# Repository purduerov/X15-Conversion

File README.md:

# Readme for X15-Conversion

Whenever you make a new part, download the datasheet and save it here _**and**_ with the part in the parts library

Always pull other people's changes before beginning to work
`git pull`

Be sure to push your changes after  working on them. Run:
1. `git add .` to add any files in this directory or a subdirectory
or `git add -u` to add any modified files
2. (Optional) `git clean -nX` to see what ignored files can be removed
	`git clean -fX` removes ignored files (Eagle backups)
3. `git commit -m "helpful commit message"` with a description of the work that you did
4. `git push` to push your work to github

Other helpful commands
* `git status` says information about modified and staged files
* `git log` shows the recent commits of the repository
* `git log filename.extension` show the recent commits for just that file
* `git checkout first-couple-letter-of-commit-id` lets you go back to a previous version
* `git checkout master` brings you back to the latest commit
* `git tag` lists the tags
* `git tag -a orderX -m "the version of the board placed for the X'th order"` tag a specific commit
* `git push --tags` needed to push tags to remote
* `git show orderX` show the commit log for the given tag
* `git checkout orderX` go back and interact with the files at the tagged commit

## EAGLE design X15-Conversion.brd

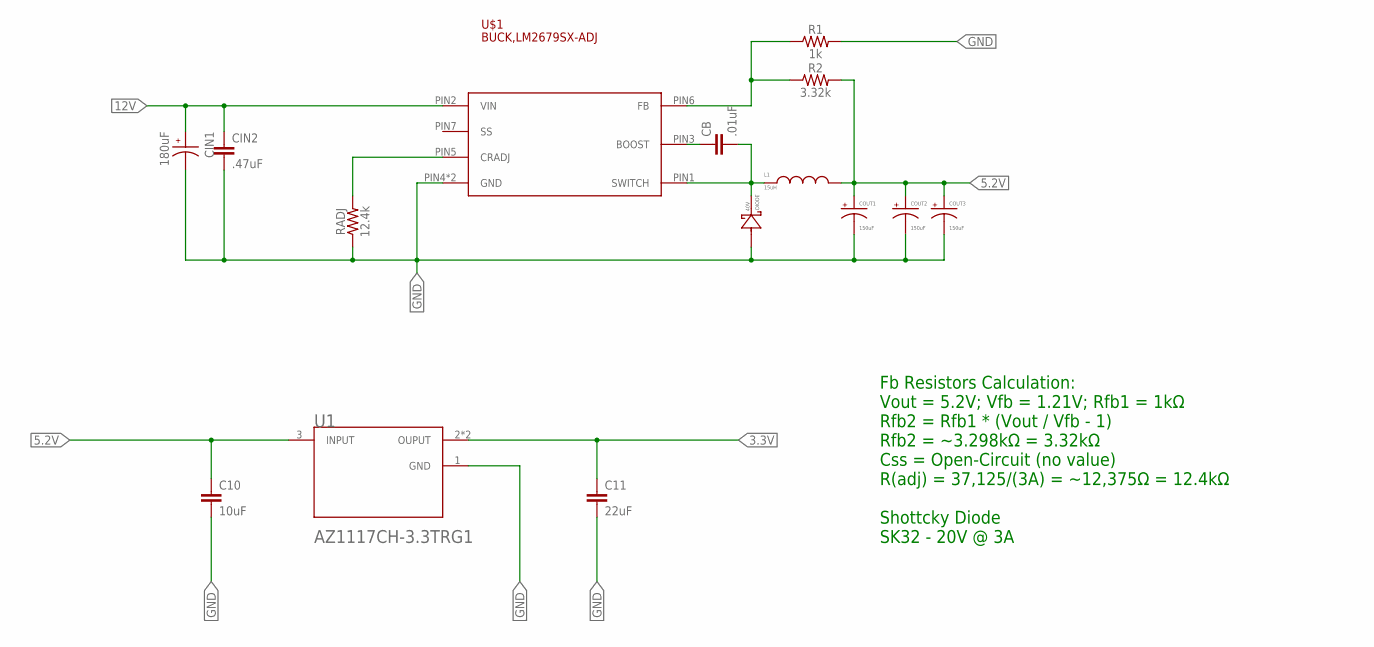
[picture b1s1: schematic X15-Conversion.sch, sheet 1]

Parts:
C10: 10uF; 0603
C11: 22uF; 0603
CB: .01uF; 0603
CIN1: 180uF; CAP_EEEFKE181XSP
CIN2: .47uF; 0603
COUT1, COUT2, COUT3: 150uF; 2917(7343-31-METRIC)
DIODE: 40V; DO214AC
L1: 15uH; HCMA1305
R1: 1k; 0603
R2: 3.32k; 0603
RADJ: 12.4k; 0603
U1: LINEAR,AZ1117CR-3.3TRG1DIODES_AZ1117CH-3.3TRG1_0_0; LINEAR,AZ1117CR-3.3TRG1
U$1: BUCK,LM2679SX-ADJ

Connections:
3.3V: C11.1, U1.2 (OUPUT), U1.4 (OUPUT); also elsewhere on the board
5.2V: C10.1, COUT1.+, COUT2.+, COUT3.+, L1.2, R2.2, U1.3 (INPUT); also elsewhere on the board
12V: CIN1.1, CIN2.1, U$1.PIN2 (VIN); also elsewhere on the board
BOOST: CB.1, U$1.PIN3 (BOOST)
CRADJ: RADJ.2, U$1.PIN5 (CRADJ)
FB: R1.1, R2.1, U$1.PIN6 (FB)
GND: C10.2, C11.2, CIN1.2, CIN2.2, COUT1.-, COUT2.-, COUT3.-, DIODE.A (2), R1.2, RADJ.1, U1.1 (GND), U$1.PIN4 (GND), U$1.PIN8 (GND); also elsewhere on the board
SWITCH: CB.2, DIODE.C (1), L1.1, U$1.PIN1 (SWITCH)

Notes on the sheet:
Fb Resistors Calculation: Vout = 5.2V; Vfb = 1.21V; Rfb1 = 1kΩ Rfb2 = Rfb1 * (Vout / Vfb - 1) Rfb2 = ~3.298kΩ = 3.32kΩ Css = Open-Circuit (no value) R(adj) = 37,125/(3A) = ~12,375Ω = 12.4kΩ Shottcky Diode SK32 - 20V @ 3A

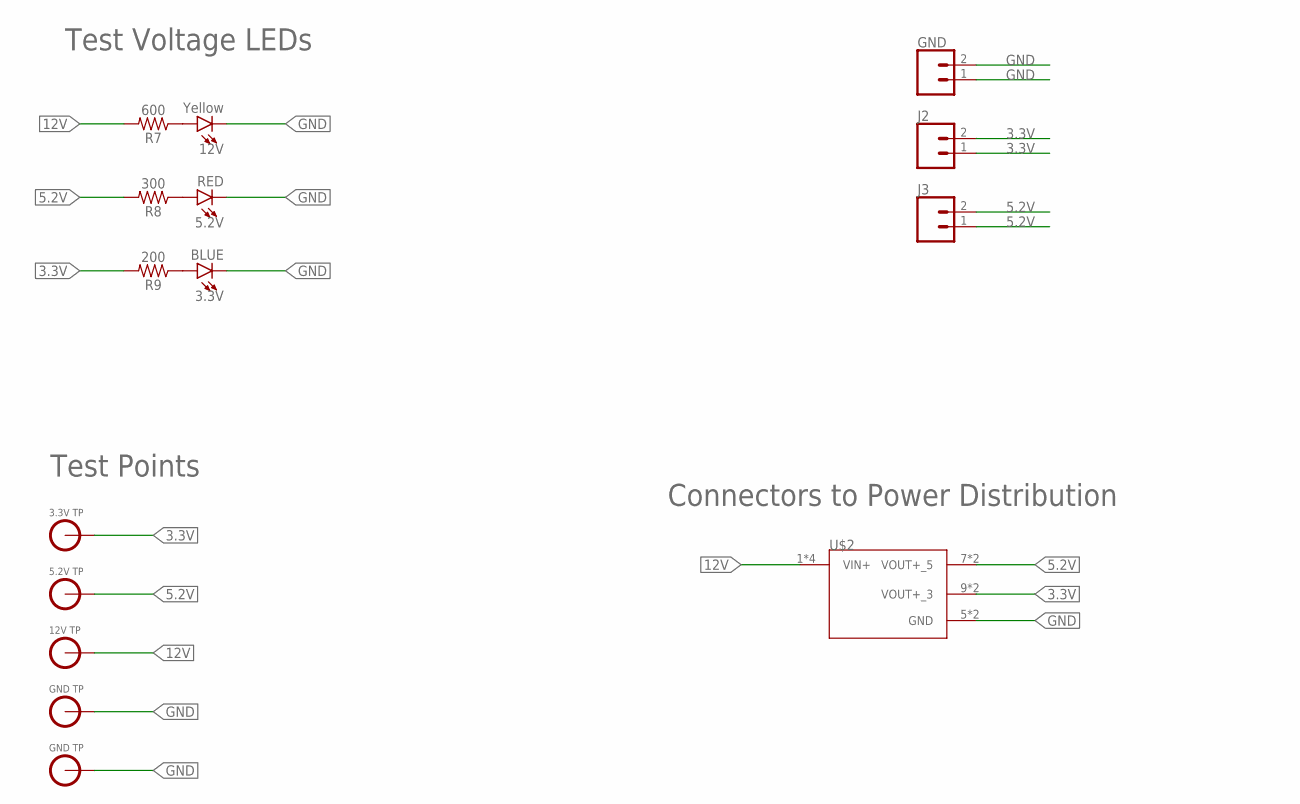
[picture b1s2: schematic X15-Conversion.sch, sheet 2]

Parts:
3.3V: BLUE; LED-0603
5.2V: RED; LED-0603
12V: Yellow; LED-0603
GND: CONN_02; 1X02
J2, J3: CONN_02; 1X02
R7: 600; 0603
R8: 300; 0603
R9: 200; 0603
U$2: CONVERSION-DISTRIBUTION; TSW-105-05-G-S(C-D)
U$8: 3.3V_TESTPOINT
U$9: 5.2V_TESTPOINT
U$10: 12V_TESTPOINT
U$11, U$12: GND_TESTPOINT

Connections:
3.3V: J2.1, J2.2, R9.2, U$2.9 (VOUT+_3), U$2.10 (VOUT+_3), U$8.3.3V; also elsewhere on the board
5.2V: J3.1, J3.2, R8.2, U$2.7 (VOUT+_5), U$2.8 (VOUT+_5), U$9.5.2V; also elsewhere on the board
12V: R7.2, U$2.1 (VIN+), U$2.2 (VIN+), U$2.3 (VIN+), U$2.4 (VIN+), U$10.12V; also elsewhere on the board
GND: 3.3V.C, 5.2V.C, 12V.C, GND.1, GND.2, U$2.5 (GND), U$2.6 (GND), U$11.GND, U$12.GND; also elsewhere on the board
unnamed: 12V.A, R7.1
unnamed: 5.2V.A, R8.1
unnamed: 3.3V.A, R9.1

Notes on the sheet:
Connectors to Power Distribution
Test Points
Test Voltage LEDs

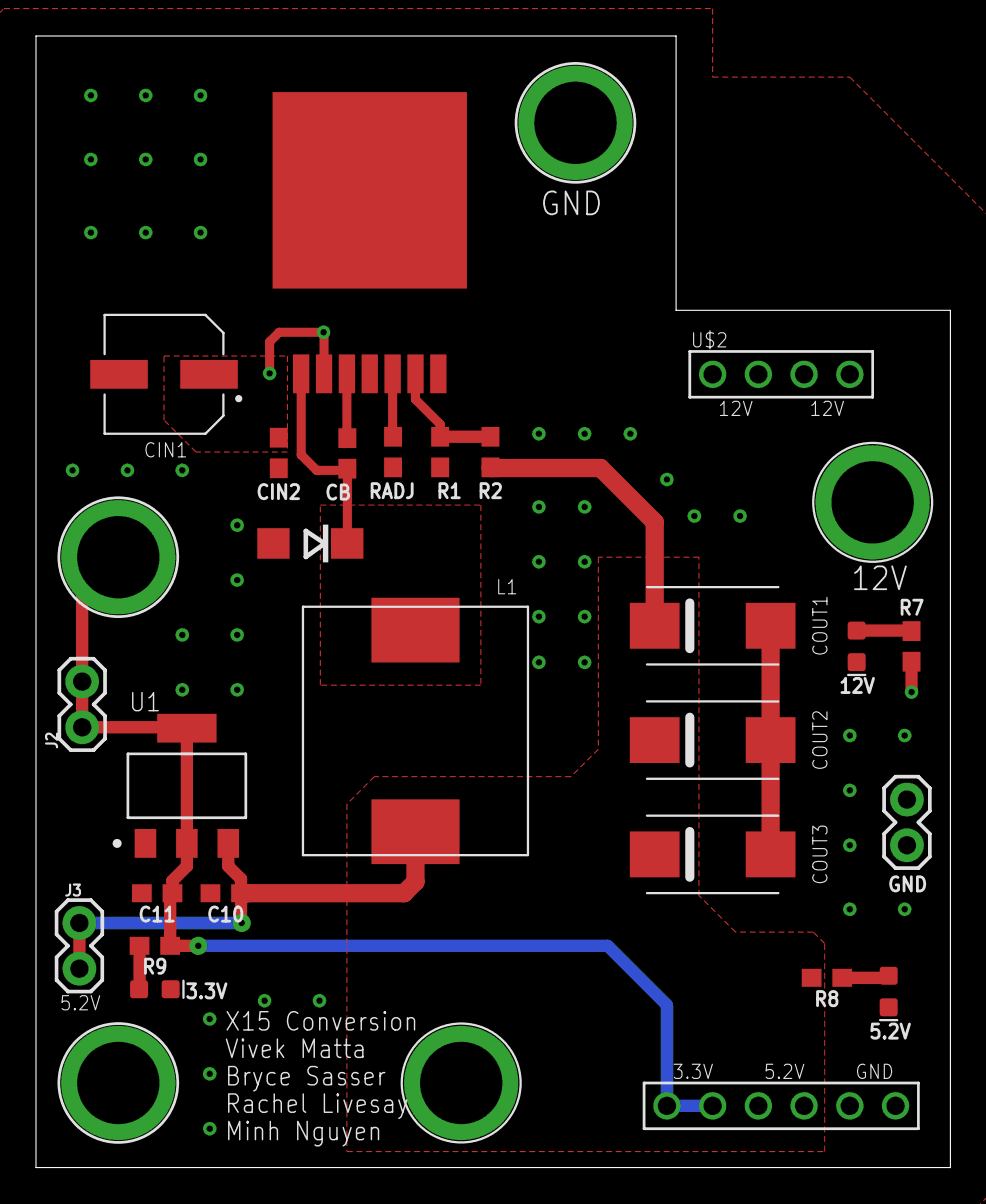
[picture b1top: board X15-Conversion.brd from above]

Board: 2 copper layers, 50.8 x 62.9 mm, 30 parts (0 on the bottom side), 11 nets.

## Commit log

2022-09-21 Create X15-Conversion.sch
    First commit to ROV
2022-10-15 Board review submission
2022-10-15 Second commit to board review
2022-10-15 added some cool files
2022-10-15 edited some part names
2022-10-15 added files
2022-10-15 Changed the GND
2022-10-18 board dimensions
2022-10-20 Changed the diode
2022-10-22 Fixed a lot of errors and debugged
2022-10-22 added wite
2022-10-22 deleted wire
2022-10-22 got rid of dumb files
2022-10-22 Revert "Merge branch 'master' of https://github.com/purduerov/X15-Conversion"
    This reverts commit 41817e178b7c3d64232767e30bfff53a28a489f7, reversing
    changes made to 9f5667108a341ebdd134b7c2334aa0d8aa0ab67e.
2022-10-22 Revert "Revert "Merge branch 'master' of https://github.com/purduerov/X15-Conversion""
    This reverts commit 3946a35888136fdb14d8eaf85822cd7069644279.
2022-10-22 Added on board
2022-10-27 Changed some compnoents
2022-11-02 deleted not good files
2022-11-02 test
2022-11-03 Added stuff to board
2022-11-05 Update Library
2022-11-11 added some stuff to board
2022-11-11 Finalized Board for Review
2022-11-12 Edited suggestions given by Bryce
2022-11-12 Edited some minor adj
2022-11-12 Minh da best
2022-11-17 added test points
2022-11-30 Chenaged some cool stuff you know
2022-12-01 Changed size in VIA
2022-12-01 Changed the fonts
2022-12-03 Changed some wires
2022-12-03 Added vias to ground
2022-12-03 Added images
2022-12-07 Changed label
2022-12-08 got rid of dash
2022-12-08 Added labels to the lights
2022-12-08 added pdf
2023-02-16 CHanged pins to the right order
2023-02-16 changed pins
2023-02-16 Fix X15 Conversion

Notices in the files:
parts and their libraries:
SparkFun-Capacitors: Licensing: Creative Commons ShareAlike 4.0 International - https://creativecommons.org/licenses/by-sa/4.0
